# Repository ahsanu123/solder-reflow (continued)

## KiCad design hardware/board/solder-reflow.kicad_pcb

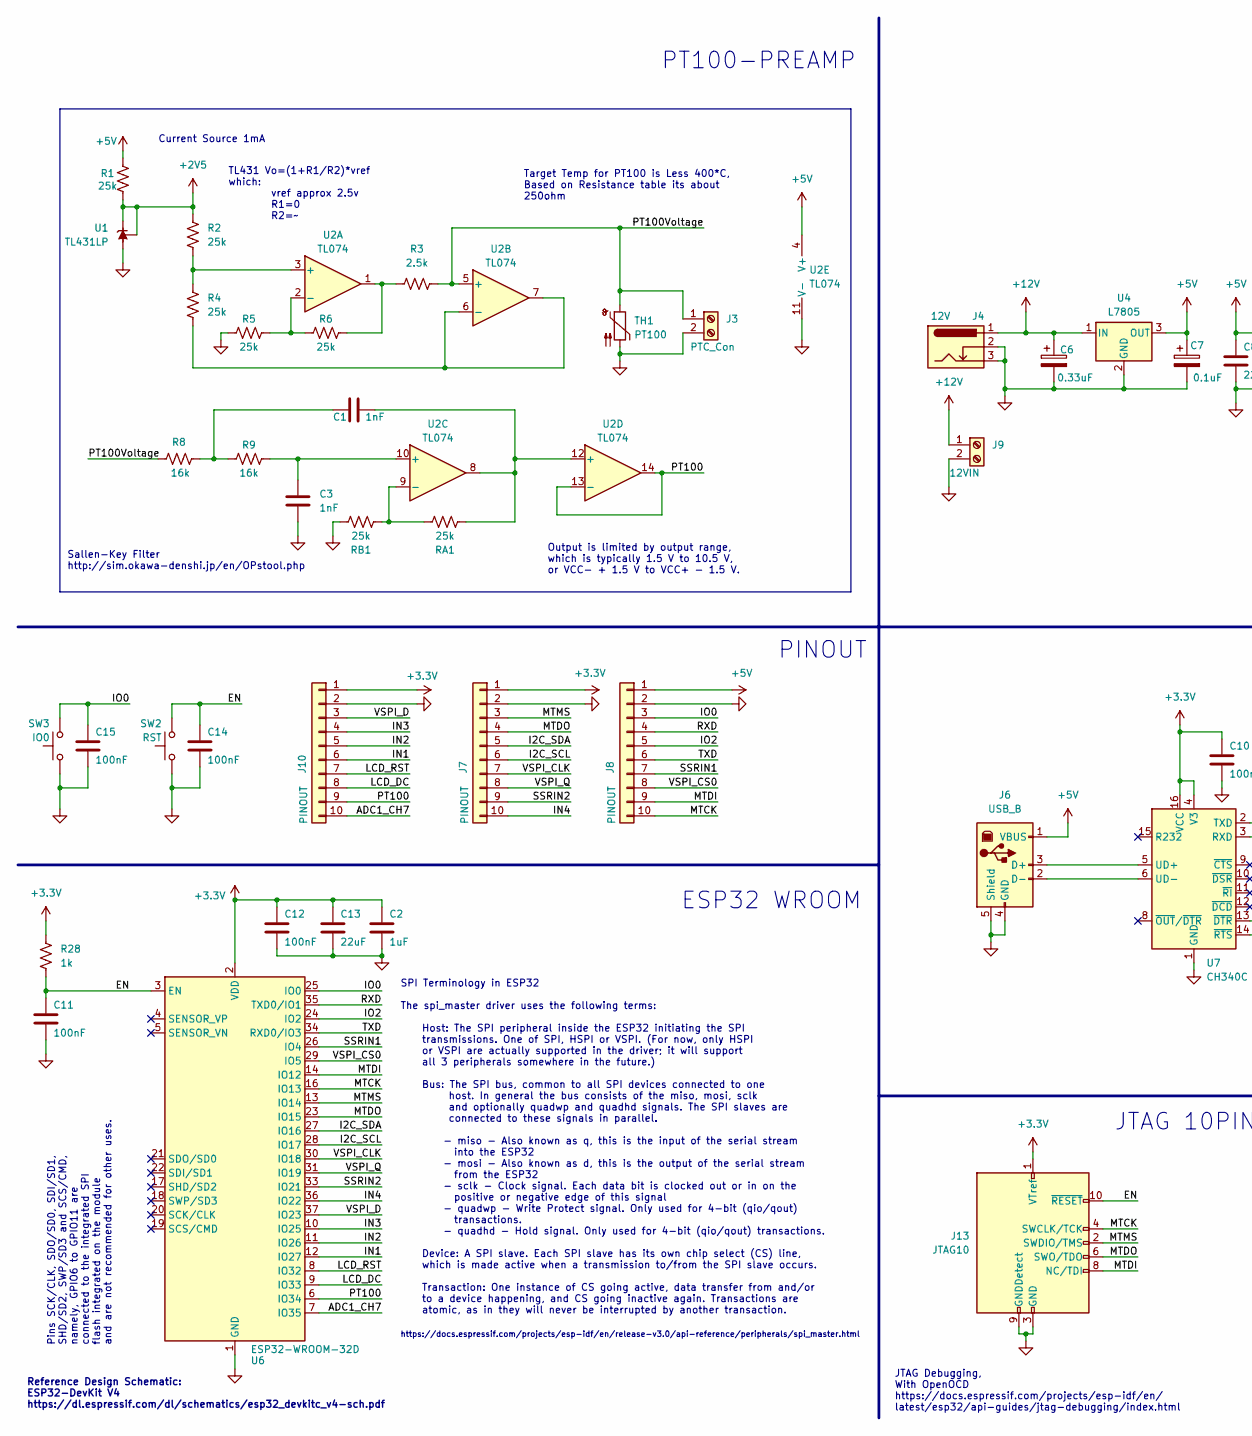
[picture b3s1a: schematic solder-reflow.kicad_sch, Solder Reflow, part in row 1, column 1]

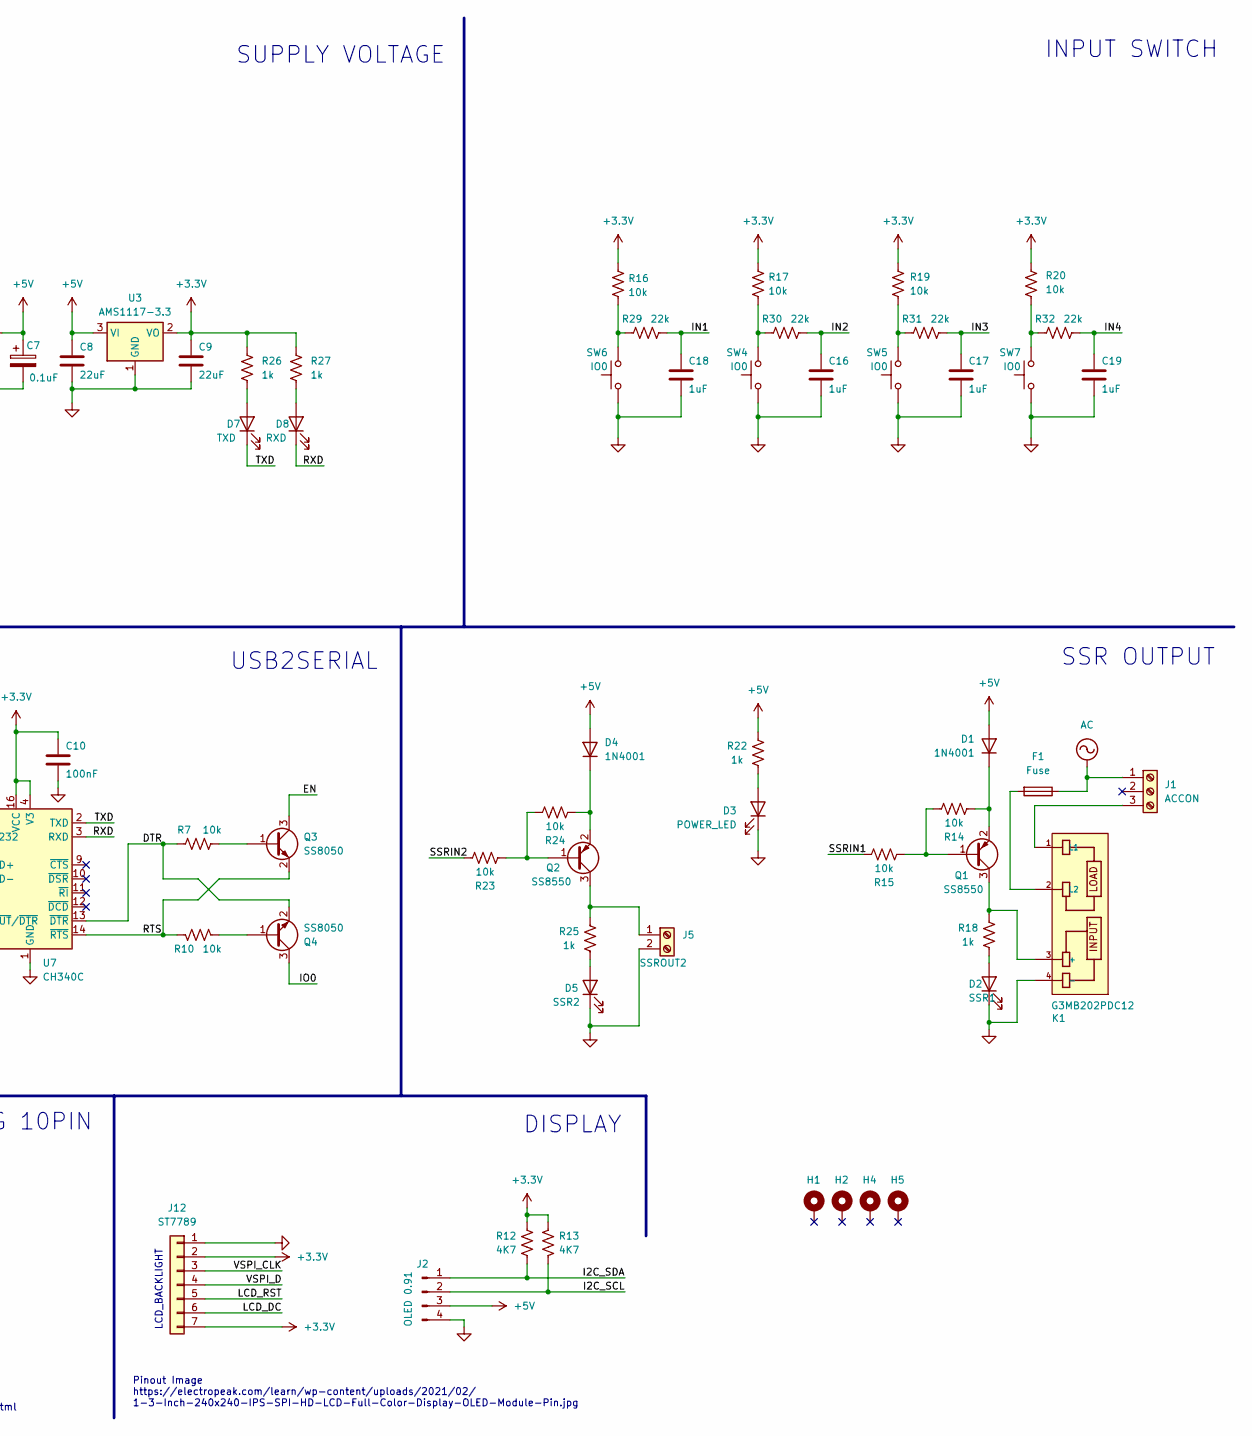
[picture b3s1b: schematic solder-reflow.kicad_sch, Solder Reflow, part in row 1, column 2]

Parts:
C1, C3: 1nF; C_1206_3216Metric_Pad1.33x1.80mm_HandSolder
C2, C16, C17, C18, C19: 1uF; C_1206_3216Metric_Pad1.33x1.80mm_HandSolder
C6: 0.33uF; C_1206_3216Metric_Pad1.33x1.80mm_HandSolder
C7: 0.1uF; C_1206_3216Metric_Pad1.33x1.80mm_HandSolder
C8, C9, C13: 22uF; C_1206_3216Metric_Pad1.33x1.80mm_HandSolder
C10, C11, C12, C14, C15: 100nF; C_1206_3216Metric_Pad1.33x1.80mm_HandSolder
D1, D4: 1N4001; D_SOD-123
D2: SSR1; LED_2010_5025Metric_Pad1.52x2.65mm_HandSolder
D3: POWER_LED; LED_2010_5025Metric_Pad1.52x2.65mm_HandSolder
D5: SSR2; LED_2010_5025Metric_Pad1.52x2.65mm_HandSolder
D7: TXD; LED_2010_5025Metric_Pad1.52x2.65mm_HandSolder
D8: RXD; LED_2010_5025Metric_Pad1.52x2.65mm_HandSolder
F1: Fuse; Fuseholder_Littelfuse_100_series_5x30mm
H1, H2, H4, H5: MountingHole_Pad; MountingHole_3.2mm_M3_DIN965_Pad
J1: ACCON; TerminalBlock_MetzConnect_Type055_RT01503HDWU_1x03_P5.00mm_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
J2: OLED 0.91; PinHeader_1x04_P2.54mm_Vertical
J3: PTC_Con; TerminalBlock_MetzConnect_Type011_RT05502HBWC_1x02_P5.00mm_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
J4: 12V; BarrelJack_Horizontal
J5: SSROUT2; TerminalBlock_MetzConnect_Type011_RT05502HBWC_1x02_P5.00mm_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
J6: USB_B; USB_B_OST_USB-B1HSxx_Horizontal
J7, J8, J10: PINOUT; PinHeader_1x10_P2.54mm_Vertical
J9: 12VIN; TerminalBlock_MetzConnect_Type011_RT05502HBWC_1x02_P5.00mm_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
J12: ST7789; PinSocket_1x07_P2.54mm_Vertical
J13: JTAG10; PinHeader_2x05_P2.54mm_Vertical
K1: G3MB202PDC12; RELAY_G3MB202PDC12; PARTREV N/A
Q1, Q2: SS8550; SOT-23_Handsoldering
Q3, Q4: SS8050; SOT-23_Handsoldering
R1, R2, R4, R5, R6: 25k; R_0805_2012Metric_Pad1.20x1.40mm_HandSolder
R3: 2.5k; R_0805_2012Metric_Pad1.20x1.40mm_HandSolder
R7, R10, R14, R15, R16, R17, R19, R20, R23, R24: 10k; R_0805_2012Metric_Pad1.20x1.40mm_HandSolder
R8, R9: 16k; R_0805_2012Metric_Pad1.20x1.40mm_HandSolder
R12, R13: 4K7; R_0805_2012Metric_Pad1.20x1.40mm_HandSolder
R18, R22, R25, R26, R27, R28: 1k; R_0805_2012Metric_Pad1.20x1.40mm_HandSolder
R29, R30, R31, R32: 22k; R_0805_2012Metric_Pad1.20x1.40mm_HandSolder
RA1: 25k; R_0805_2012Metric_Pad1.20x1.40mm_HandSolder
RB1: 25k; R_0805_2012Metric_Pad1.20x1.40mm_HandSolder
SW2: RST; SW_SPST_B3S-1000
SW3, SW4, SW5, SW6, SW7: IO0; SW_SPST_B3S-1000
TH1: PT100; TO-92-2_Horizontal2
U1: TL431LP; TO-92_Inline_Wide
U2: TL074; SOIC-14_3.9x8.7mm_P1.27mm
U3: AMS1117-3.3; SOT-223-3_TabPin2
U4: L7805; TO-220F-3_Horizontal_TabDown
U6: ESP32-WROOM-32D
U7: CH340C; SOIC-16_3.9x9.9mm_P1.27mm

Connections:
+2V5: R1.1, R2.1, U1.1 (REF), U1.3 (K)
+3.3V: C2.1, C9.1, C10.1, C12.1, C13.1, J7.1, J10.1, J12.2, J12.7, J13.1 (VTref), R12.2, R13.2, R16.1, R17.1, R19.1, R20.1, R26.1, R27.1, R28.1, U3.2 (VO), U6.2 (VDD), U7.4 (V3), U7.16 (VCC); also elsewhere on the board
+5V: C7.1, C8.1, D1.2 (A), D4.2 (A), J2.3, J6.1 (VBUS), J8.1, R1.2, R22.2, U2.4 (V+), U3.3 (VI), U4.3 (OUT)
+12V: C6.1, J4.1, J9.1, U4.1 (IN)
/ADC1_CH7: J10.10, U6.7 (IO35)
/DTR: Q4.2 (E), R7.2, U7.13 (~DTR)
/EN: C11.1, C14.1, J13.10 (~RESET), Q3.3 (C), R28.2, SW2.2, U6.3 (EN)
/I2C_SCL: J2.2, J7.6, R13.1, U6.28 (IO17)
/I2C_SDA: J2.1, J7.5, R12.1, U6.27 (IO16)
/IN1: C18.1, J10.6, R29.1, U6.12 (IO27)
/IN2: C16.1, J10.5, R30.1, U6.11 (IO26)
/IN3: C17.1, J10.4, R31.1, U6.10 (IO25)
/IN4: C19.1, J7.10, R32.1, U6.36 (IO22)
/IO0: C15.1, J8.3, Q4.3 (C), SW3.2, U6.25 (IO0)
/LCD_CS: J8.5, U6.24 (IO2); also elsewhere on the board
/LCD_DC: J10.8, J12.6, U6.9 (IO33); also elsewhere on the board
/LCD_RST: J10.7, J12.5, U6.8 (IO32); also elsewhere on the board
/MTCK: J8.10, J13.4 (SWCLK/TCK), U6.16 (IO13)
/MTDI: J8.9, J13.8 (NC/TDI), U6.14 (IO12)
/MTDO: J7.4, J13.6 (SWO/TDO), U6.23 (IO15)
/MTMS: J7.3, J13.2 (SWDIO/TMS), U6.13 (IO14)
/PT100: J10.9, U2.13 (-), U2.14, U6.6 (IO34)
/PT100Voltage: J3.1, R3.1, R8.2, TH1.1, U2.5 (+)
/RTS: Q3.2 (E), R10.2, U7.14 (~RTS)
/RXD: D8.1 (K), J8.4, U6.35 (TXD0/IO1), U7.3 (RXD)
/SSRIN1: J8.7, R15.1, U6.26 (IO4)
/SSRIN2: J7.9, R23.1, U6.33 (IO21)
/TXD: D7.1 (K), J8.6, U6.34 (RXD0/IO3), U7.2 (TXD)
/VSPI_CLK: J7.7, J12.3, U6.30 (IO18); also elsewhere on the board
/VSPI_CS0: J8.8, U6.29 (IO5)
/VSPI_D: J10.3, J12.4, U6.37 (IO23); also elsewhere on the board
/VSPI_Q: J7.8, U6.31 (IO19)
AC: F1.1, J1.1
GND: C2.2, C3.2, C6.2, C7.2, C8.2, C9.2, C10.2, C11.2, C12.2, C13.2, C14.2, C15.2, C16.2, C17.2, C18.2, C19.2, D2.1 (K), D3.1 (K), D5.1 (K), J2.4, J3.2, J4.2, J4.3, J5.2, J6.4 (GND), J6.5 (Shield), J7.2, J8.2, J9.2, J10.2, J12.1, J13.3 (GND), J13.5 (GND), J13.9 (GNDDetect), K1.4 (-), R5.1, RB1.1, SW2.1, SW3.1, SW4.1, SW5.1, SW6.1, SW7.1, TH1.2, U1.2 (A), U2.11 (V-), U3.1 (GND), U4.2 (GND), U6.1 (GND), U6.15 (GND), U6.38 (GND), U6.39 (GND), U7.1 (GND); also elsewhere on the board
unnamed: C1.2, R8.1, R9.2
unnamed: D1.1 (K), Q1.2 (E), R14.2
unnamed: D2.2 (A), R18.1
unnamed: D3.2 (A), R22.1
unnamed: D4.1 (K), Q2.2 (E), R24.2
unnamed: D5.2 (A), R25.1
unnamed: D7.2 (A), R26.2
unnamed: D8.2 (A), R27.2
unnamed: J1.3, K1.1 (L1)
unnamed: J5.1, Q2.3 (C), R25.2
unnamed: J6.3 (D+), U7.5 (UD+)
unnamed: J6.2 (D-), U7.6 (UD-)
unnamed: K1.3 (+), Q1.3 (C), R18.2
unnamed: F1.2, K1.2 (L2)
unnamed: Q1.1 (B), R14.1, R15.2
unnamed: Q2.1 (B), R23.2, R24.1
unnamed: Q3.1 (B), R7.1
unnamed: Q4.1 (B), R10.1
unnamed: R3.2, R6.1, U2.1
unnamed: R16.2, R29.2, SW6.2
unnamed: R17.2, R30.2, SW4.2
unnamed: R19.2, R31.2, SW5.2
unnamed: R20.2, R32.2, SW7.2
unnamed: R2.2, R4.1, U2.3 (+)
unnamed: R5.2, R6.2, U2.2 (-)
unnamed: R4.2, U2.6 (-), U2.7
unnamed: C3.1, R9.1, U2.10 (+)
unnamed: RA1.1, RB1.2, U2.9 (-)
unnamed: C1.1, RA1.2, U2.8, U2.12 (+)

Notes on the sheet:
Sallen-Key Filter http://sim.okawa-denshi.jp/en/OPstool.php
Reference Design Schematic: ESP32-DevKit V4 https://dl.espressif.com/dl/schematics/esp32_devkitc_v4-sch.pdf
SUPPLY VOLTAGE
JTAG 10PIN
Output is limited by output range, which is typically 1.5 V to 10.5 V, or VCC- + 1.5 V to VCC+ - 1.5 V.
Pinout Image https://electropeak.com/learn/wp-content/uploads/2021/02/ 1-3-Inch-240x240-IPS-SPI-HD-LCD-Full-Color-Display-OLED-Module-Pin.jpg
ESP32 WROOM
PT100-PREAMP
DISPLAY
Pins SCK/CLK, SDO/SD0, SDI/SD1, SHD/SD2, SWP/SD3 and SCS/CMD, namely, GPIO6 to GPIO11 are connected to the integrated SPI flash integrated on the module and are not recommended for other uses.
TL431 Vo=(1+R1/R2)*vref which: vref approx 2.5v R1=0 R2=~
Target Temp for PT100 is Less 400*C, Based on Resistance table its about 250ohm
PINOUT
Current Source 1mA
JTAG Debugging, With OpenOCD https://docs.espressif.com/projects/esp-idf/en/ latest/esp32/api-guides/jtag-debugging/index.html
SPI Terminology in ESP32 The spi_master driver uses the following terms: Host: The SPI peripheral inside the ESP32 initiating the SPI transmissions. One of SPI, HSPI or VSPI. (For now, only HSPI or VSPI are actually supported in the driver; it will support all 3 peripherals somewhere in the future.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
LCD_BACKLIGHT
USB2SERIAL
INPUT SWITCH
SSR OUTPUT

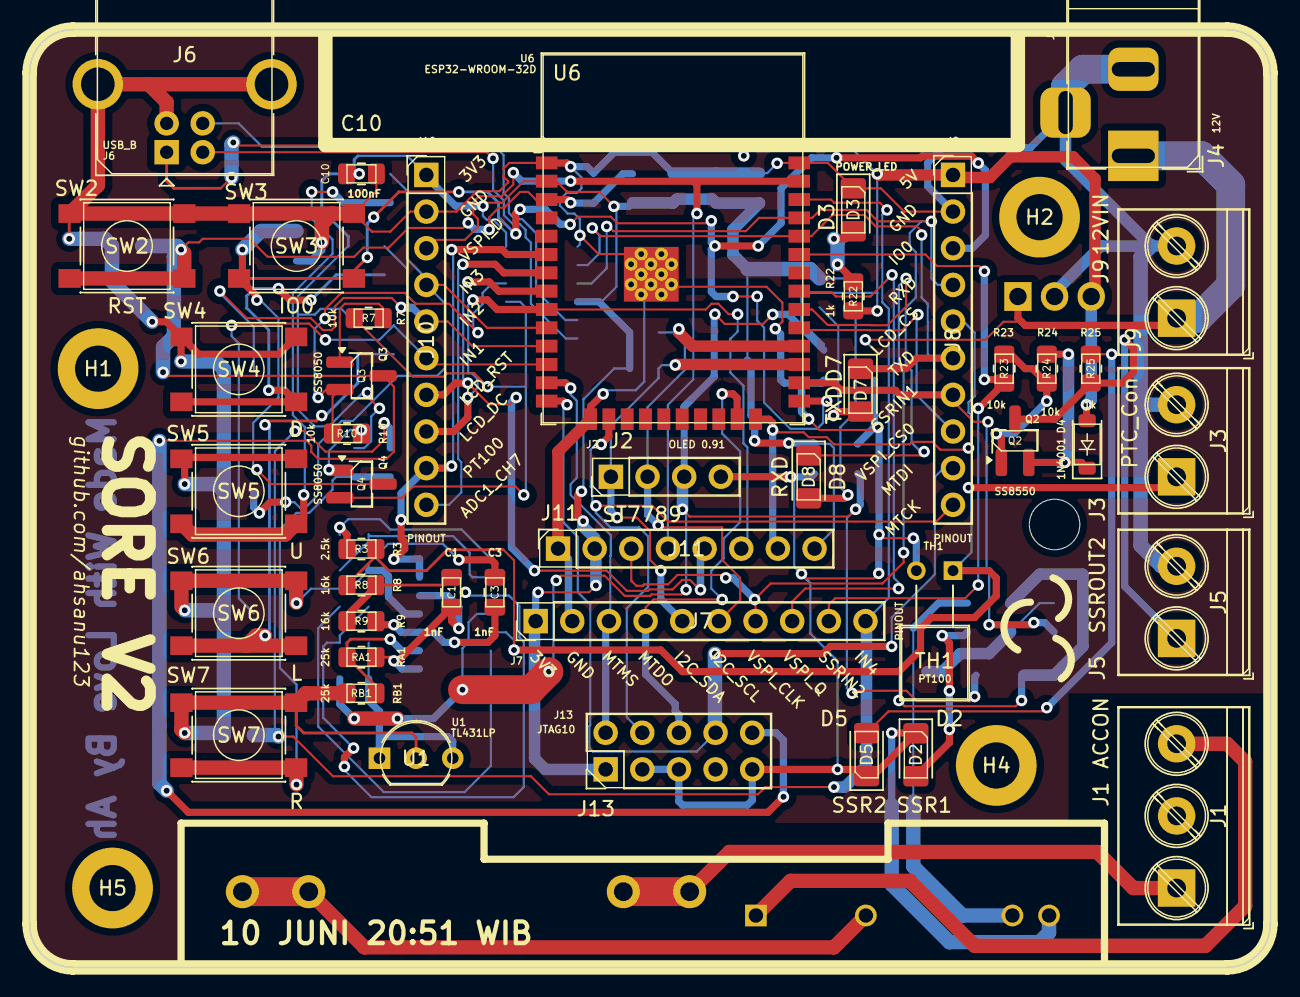
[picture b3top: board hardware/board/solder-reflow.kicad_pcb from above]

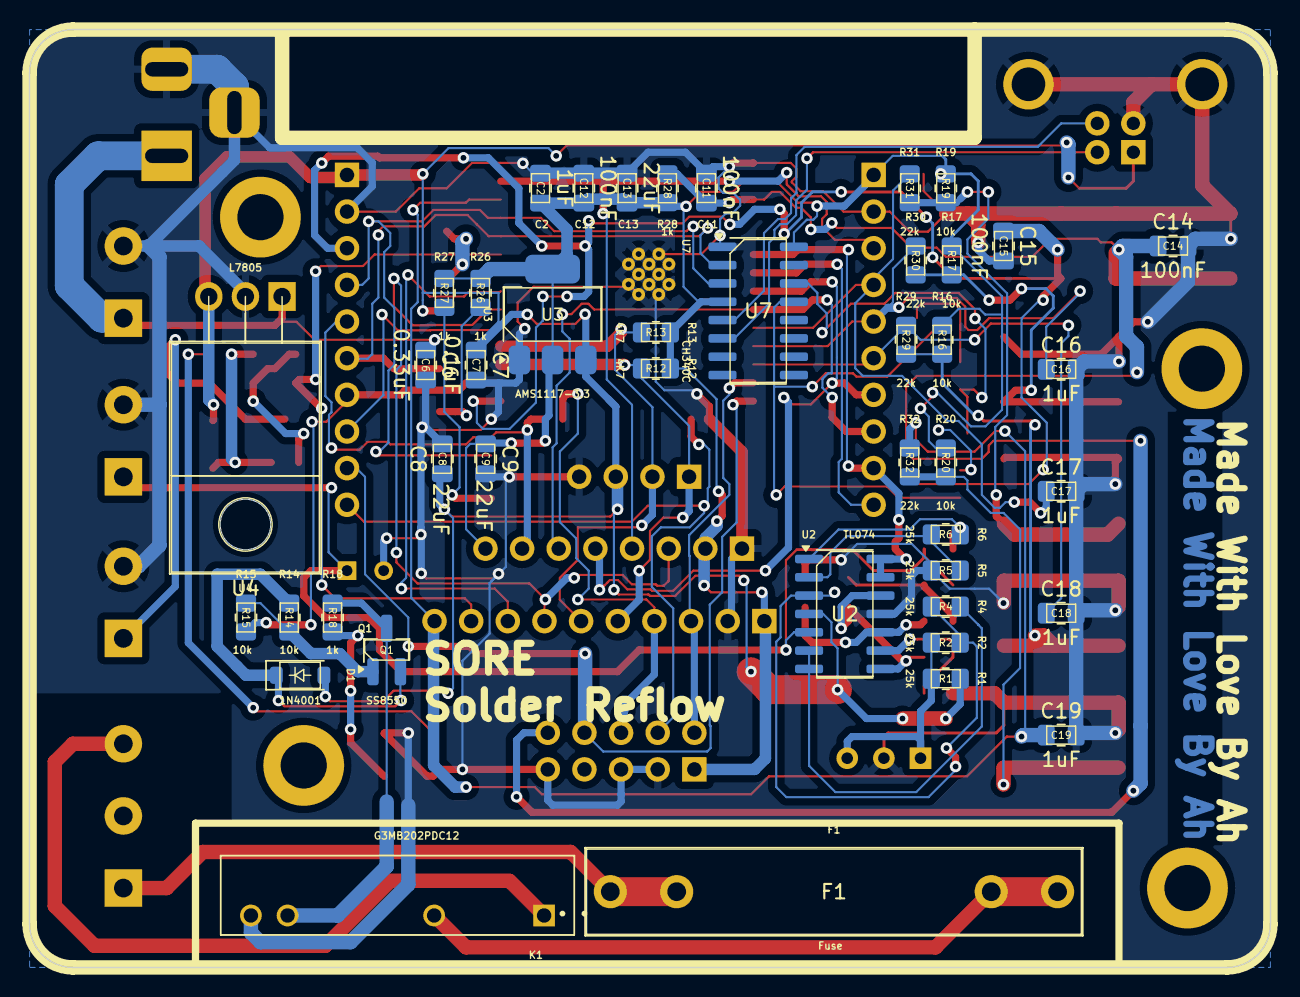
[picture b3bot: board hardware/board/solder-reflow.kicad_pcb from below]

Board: 2 copper layers, 86.0 x 65.0 mm, 91 parts (43 on the bottom side), 63 nets.

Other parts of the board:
J11: ST7789; PinSocket_1x08_P2.54mm_Vertical

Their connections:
+3.3V: J11.2, J11.8; also elsewhere on the board
/LCD_CS: J11.7; also elsewhere on the board
/LCD_DC: J11.6; also elsewhere on the board
/LCD_RST: J11.5; also elsewhere on the board
/VSPI_CLK: J11.3; also elsewhere on the board
/VSPI_D: J11.4; also elsewhere on the board
GND: J11.1; also elsewhere on the board

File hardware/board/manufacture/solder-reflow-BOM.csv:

"Id";"Designator";"Footprint";"Quantity";"Designation";"Supplier and ref";
1;"J9";"TerminalBlock_Phoenix_PT-1,5-2-5.0-H_1x02_P5.00mm_Horizontal";1;"12VIN";;;
2;"J3";"TerminalBlock_Phoenix_PT-1,5-2-5.0-H_1x02_P5.00mm_Horizontal";1;"PTC_Con";;;
3;"J5";"TerminalBlock_Phoenix_PT-1,5-2-5.0-H_1x02_P5.00mm_Horizontal";1;"SSROUT2";;;
4;"D8";"LED_2010_5025Metric_Pad1.52x2.65mm_HandSolder";1;"RXD";;;
5;"R9,R8";"R_0805_2012Metric_Pad1.20x1.40mm_HandSolder";2;"16k";;;
6;"H1,H2,H5,H4";"MountingHole_3.2mm_M3_DIN965_Pad";4;"MountingHole_Pad";;;
7;"R23,R10,R7,R24,R14,R17,R15,R20,R19,R16";"R_0805_2012Metric_Pad1.20x1.40mm_HandSolder";10;"10k";;;
8;"U1";"TO-92_Inline_Wide";1;"TL431LP";;;
9;"U6";"ESP32-WROOM-32D";1;"ESP32-WROOM-32D";;;
10;"D3";"LED_2010_5025Metric_Pad1.52x2.65mm_HandSolder";1;"POWER_LED";;;
11;"RA1,RB1,R6,R4,R2,R5,R1";"R_0805_2012Metric_Pad1.20x1.40mm_HandSolder";7;"25k";;;
12;"J6";"USB_B_OST_USB-B1HSxx_Horizontal";1;"USB_B";;;
13;"R25,R22,R26,R27,R28,R18";"R_0805_2012Metric_Pad1.20x1.40mm_HandSolder";6;"1k";;;
14;"SW2";"SW_SPST_B3S-1000";1;"RST";;;
15;"Q3,Q4";"SOT-23_Handsoldering";2;"SS8050";;;
16;"C10,C11,C15,C14,C12";"C_1206_3216Metric_Pad1.33x1.80mm_HandSolder";5;"100nF";;;
17;"SW5,SW7,SW6,SW4,SW3";"SW_SPST_B3S-1000";5;"IO0";;;
18;"C3,C1";"C_1206_3216Metric_Pad1.33x1.80mm_HandSolder";2;"1nF";;;
19;"J13";"PinHeader_2x05_P2.54mm_Vertical";1;"JTAG10";;;
20;"J12";"PinSocket_1x07_P2.54mm_Vertical";1;"ST7789";;;
21;"R3";"R_0805_2012Metric_Pad1.20x1.40mm_HandSolder";1;"2.5k";;;
22;"J8,J7,J10";"PinHeader_1x10_P2.54mm_Vertical";3;"PINOUT";;;
23;"J1";"TerminalBlock_MetzConnect_Type055_RT01503HDWU_1x03_P5.00mm_Horizontal";1;"ACCON";;;
24;"D2";"LED_2010_5025Metric_Pad1.52x2.65mm_HandSolder";1;"SSR1";;;
25;"J2";"PinHeader_1x04_P2.54mm_Vertical";1;"OLED 0.91";;;
26;"D7";"LED_2010_5025Metric_Pad1.52x2.65mm_HandSolder";1;"TXD";;;
27;"Q2,Q1";"SOT-23_Handsoldering";2;"SS8550";;;
28;"J4";"BarrelJack_Horizontal";1;"12V";;;
29;"D4,D1";"D_SOD-123";2;"1N4001";;;
30;"D5";"LED_2010_5025Metric_Pad1.52x2.65mm_HandSolder";1;"SSR2";;;
31;"R31,R32,R29,R30";"R_0805_2012Metric_Pad1.20x1.40mm_HandSolder";4;"22k";;;
32;"C19,C17,C16,C18,C2";"C_1206_3216Metric_Pad1.33x1.80mm_HandSolder";5;"1uF";;;
33;"U7";"SOIC-16_3.9x9.9mm_P1.27mm";1;"CH340C";;;
34;"R12,R13";"R_0805_2012Metric_Pad1.20x1.40mm_HandSolder";2;"4K7";;;
35;"C8,C13,C9";"C_1206_3216Metric_Pad1.33x1.80mm_HandSolder";3;"22uF";;;
36;"U3";"SOT-223-3_TabPin2";1;"AMS1117-3.3";;;
37;"C6";"C_1206_3216Metric_Pad1.33x1.80mm_HandSolder";1;"0.33uF";;;
38;"TH1";"TO-92-2_Horizontal2";1;"PT100";;;
39;"K1";"RELAY_G3MB202PDC12";1;"G3MB202PDC12";;;
40;"F1";"Fuseholder_Littelfuse_100_series_5x30mm";1;"Fuse";;;
41;"C7";"C_1206_3216Metric_Pad1.33x1.80mm_HandSolder";1;"0.1uF";;;
42;"U2";"SOIC-14_3.9x8.7mm_P1.27mm";1;"TL074";;;
43;"U4";"TO-220F-3_Horizontal_TabDown";1;"L7805";;;

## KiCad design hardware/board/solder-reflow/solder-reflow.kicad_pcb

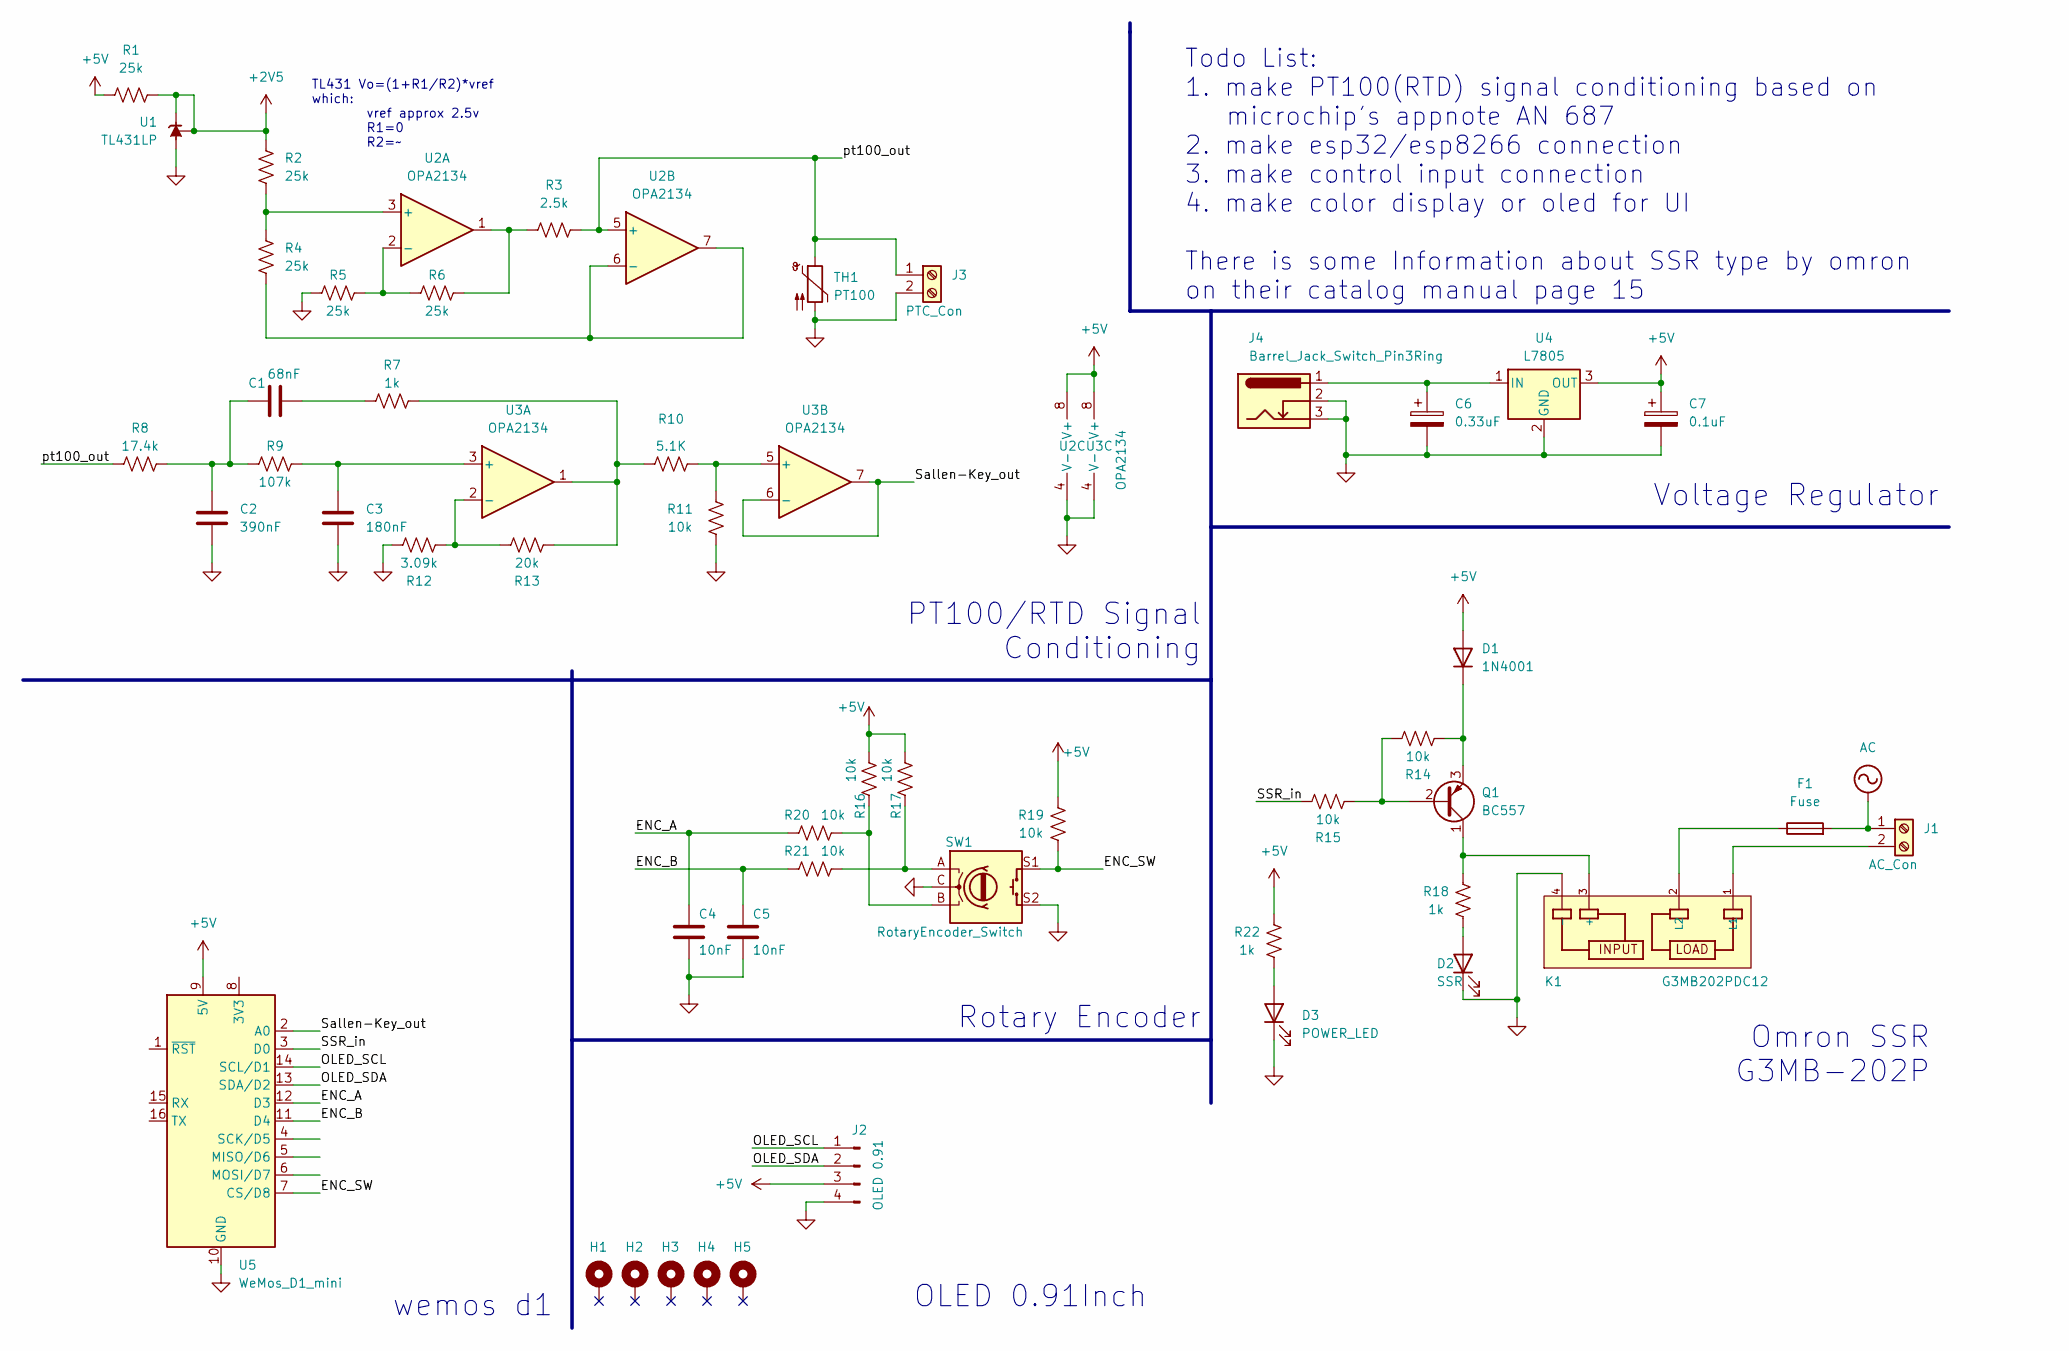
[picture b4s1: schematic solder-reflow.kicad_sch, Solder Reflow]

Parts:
C1: 68nF; C_Disc_D4.3mm_W1.9mm_P5.00mm
C2: 390nF; C_Disc_D4.3mm_W1.9mm_P5.00mm
C3: 180nF; C_Disc_D4.3mm_W1.9mm_P5.00mm
C4, C5: 10nF; C_Disc_D4.3mm_W1.9mm_P5.00mm
C6: 0.33uF; CP_Radial_D6.3mm_P2.50mm
C7: 0.1uF; CP_Radial_D6.3mm_P2.50mm
D1: 1N4001; D_DO-41_SOD81_P10.16mm_Horizontal
D2: SSR; LED_D5.0mm
D3: POWER_LED; LED_D5.0mm
F1: Fuse; Fuseholder_Littelfuse_100_series_5x30mm
H1, H2, H3, H4, H5: MountingHole_Pad; MountingHole_3.2mm_M3_DIN965_Pad
J1: AC_Con; TerminalBlock_MetzConnect_Type011_RT05502HBWC_1x02_P5.00mm_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
J2: OLED 0.91; PinHeader_1x04_P2.54mm_Vertical
J3: PTC_Con; TerminalBlock_MetzConnect_Type011_RT05502HBWC_1x02_P5.00mm_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
J4: Barrel_Jack_Switch_Pin3Ring; BarrelJack_Horizontal
K1: G3MB202PDC12; RELAY_G3MB202PDC12; PARTREV N/A
Q1: BC557; TO-92_Inline_Wide
R1, R2, R4, R5, R6: 25k; R_Axial_DIN0207_L6.3mm_D2.5mm_P10.16mm_Horizontal
R3: 2.5k; R_Axial_DIN0207_L6.3mm_D2.5mm_P10.16mm_Horizontal
R7, R18, R22: 1k; R_Axial_DIN0207_L6.3mm_D2.5mm_P10.16mm_Horizontal
R8: 17.4k; R_Axial_DIN0207_L6.3mm_D2.5mm_P10.16mm_Horizontal
R9: 107k; R_Axial_DIN0207_L6.3mm_D2.5mm_P10.16mm_Horizontal
R10: 5.1K; R_Axial_DIN0207_L6.3mm_D2.5mm_P10.16mm_Horizontal
R11, R14, R15, R16, R17, R19, R20, R21: 10k; R_Axial_DIN0207_L6.3mm_D2.5mm_P10.16mm_Horizontal
R12: 3.09k; R_Axial_DIN0207_L6.3mm_D2.5mm_P10.16mm_Horizontal
R13: 20k; R_Axial_DIN0207_L6.3mm_D2.5mm_P10.16mm_Horizontal
SW1: RotaryEncoder_Switch; RotaryEncoder_Alps_EC11E-Switch_Vertical_H20mm
TH1: PT100; TO-92-2_Horizontal2
U1: TL431LP; TO-92_Inline_Wide
U2, U3: OPA2134; DIP-8_W7.62mm_LongPads
U4: L7805; TO-220F-3_Horizontal_TabDown
U5: WeMos_D1_mini; WEMOS_D1_mini_light

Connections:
+2V5: R1.2, R2.1, U1.1 (REF), U1.3 (K)
+5V: C7.1, D1.2 (A), J2.3, R1.1, R16.2, R17.2, R19.2, R22.2, U2.8 (V+), U3.8 (V+), U4.3 (OUT), U5.9 (5V)
/ENC_A: C4.1, R20.2, U5.12 (D3)
/ENC_B: C5.1, R21.2, U5.11 (D4)
/ENC_SW: R19.1, SW1.S1, U5.7 (CS/D8)
/OLED_SCL: J2.1, U5.14 (SCL/D1)
/OLED_SDA: J2.2, U5.13 (SDA/D2)
/SSR_in: R15.1, U5.3 (D0)
/Sallen-Key_out: U3.6 (-), U3.7, U5.2 (A0)
/pt100_out: J3.1, R3.1, R8.2, TH1.1, U2.5 (+)
AC: F1.2, J1.1
GND: C2.2, C3.2, C4.2, C5.2, C6.2, C7.2, D2.1 (K), D3.1 (K), J2.4, J3.2, J4.2, J4.3, K1.4 (-), R5.1, R11.1, R12.1, SW1.C, SW1.S2, TH1.2, U1.2 (A), U2.4 (V-), U3.4 (V-), U4.2 (GND), U5.10 (GND)
unnamed: C1.1, R7.2
unnamed: C1.2, C2.1, R8.1, R9.2
unnamed: D1.1 (K), Q1.3 (E), R14.2
unnamed: D2.2 (A), R18.1
unnamed: D3.2 (A), R22.1
unnamed: J1.2, K1.1 (L1)
unnamed: K1.3 (+), Q1.1 (C), R18.2
unnamed: F1.1, K1.2 (L2)
unnamed: Q1.2 (B), R14.1, R15.2
unnamed: R3.2, R6.1, U2.1
unnamed: R7.1, R10.1, R13.2, U3.1
unnamed: R16.1, R20.1, SW1.B
unnamed: R17.1, R21.1, SW1.A
unnamed: R2.2, R4.1, U2.3 (+)
unnamed: R5.2, R6.2, U2.2 (-)
unnamed: R4.2, U2.6 (-), U2.7
unnamed: C3.1, R9.1, U3.3 (+)
unnamed: R12.2, R13.1, U3.2 (-)
unnamed: R10.2, R11.2, U3.5 (+)
unnamed: C6.1, J4.1, U4.1 (IN)

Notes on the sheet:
Voltage Regulator
wemos d1
PT100/RTD Signal Conditioning
OLED 0.91Inch
TL431 Vo=(1+R1/R2)*vref which: vref approx 2.5v R1=0 R2=~
Todo List: 1. make PT100(RTD) signal conditioning based on microchip's appnote AN 687 2. make esp32/esp8266 connection 3. make control input connection 4. make color display or oled for UI There is some Information about SSR type by omron on their catalog manual page 15
Rotary Encoder
Omron SSR G3MB-202P

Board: 2 copper layers, 51 parts (0 on the bottom side), 32 nets, no tracks yet.

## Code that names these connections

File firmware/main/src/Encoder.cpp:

#include "Encoder.h"
#include "gpio.h"
#include <cstdint>

#ifndef INCLUDE_SRC_ENCODER_CPP_
#define INCLUDE_SRC_ENCODER_CPP_

Encoder::Encoder() {

  gpio_config_t enc_ab_sw = {.pin_bit_mask =
                                 GPIO_Pin_0 | GPIO_Pin_2 | GPIO_Pin_15,
                             .mode = GPIO_MODE_INPUT,
                             .pull_up_en = GPIO_PULLUP_DISABLE,
                             .pull_down_en = GPIO_PULLDOWN_DISABLE,
                             .intr_type = GPIO_INTR_DISABLE};
  gpio_config(&enc_ab_sw);
}

float Encoder::setToTarget(float *target) {
  *target = this->_target;
  return *target;
}

float Encoder::decodeEncoder() {
  /*
   * |New state | Old State|
   * |  3 |  2  |  1 |  0  |
   *
   * */
  uint8_t rawData = (1 << !gpio_get_level(ENC_A)) | !gpio_get_level(ENC_B);
  uint8_t state = this->_oldState & 0x03;

  if (rawData & 0x04)
    state |= 0x04;
  if (rawData & 0x08)
    state |= 0x08;

  switch (state) {
  case 0:
  case 5:
  case 10:
  case 15:
    break;
  case 1:
  case 7:
  case 8:
  case 14:
    this->position += this->step;

    if (this->connectedVariable) {
      *this->connectedVariable += this->step;
    } else {
    }
    this->connectedMenu->up();
    break;
  case 2:
  case 4:
  case 11:
  case 13:
    this->position -= this->step;

    if (this->connectedVariable) {
      *this->connectedVariable -= this->step;
    } else {
    }
    this->connectedMenu->down();
    break;
  case 3:
  case 12:
    this->position += this->step * 2;

    if (this->connectedVariable) {
      *this->connectedVariable += this->step * 2;
    } else {
    }
    this->connectedMenu->up();
    break;
  default:
    this->position -= this->step * 2;

    if (this->connectedVariable) {
      *this->connectedVariable -= this->step * 2;
    } else {
    }
    this->connectedMenu->down();
    break;
  }

  this->_oldState = state >> 2;

  return this->position;
};

bool Encoder::decodeSwitch(float &target) {

  /*
   * | OLD || NEW |
   * |  0  ||  0  | no change
   * |  0  ||  1  | toggled
   * |  1  ||  0  | change
   * |  1  ||  1  | no change
   * */

  bool state = gpio_get_level(ENC_SW);

  uint8_t current = this->_oldSwitchState + state;

  if (current == 1) {
    this->_oldSwitchState = state << 1;
    this->switchState = !this->switchState;

    if (this->switchState) {
      this->connectedVariable = &target;
    } else {
      this->connectedVariable = NULL;
    }

    return this->switchState;
  } else if (current == 2) {
    this->_oldSwitchState = state;
    return this->switchState;
  } else {
    return this->switchState;
  }
}
#endif // INCLUDE_SRC_ENCODER_CPP_

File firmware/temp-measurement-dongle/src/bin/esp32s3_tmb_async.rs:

#![no_std]
#![no_main]
#![deny(
    clippy::mem_forget,
    reason = "mem::forget is generally not safe to do with esp_hal types, especially those \
    holding buffers for the duration of a data transfer."
)]
#![deny(clippy::large_stack_frames)]

use alloc::boxed::Box;
use defmt::info;
use embassy_executor::Spawner;
use embassy_time::Timer;
use embedded_hal_bus::spi::ExclusiveDevice;
use esp_hal::clock::CpuClock;
use esp_hal::delay::Delay;
use esp_hal::dma::{DmaRxBuf, DmaTxBuf};
use esp_hal::dma_buffers;
use esp_hal::gpio::{Level, Output, OutputConfig};
use esp_hal::spi::Mode;
use esp_hal::spi::master::Config;
use esp_hal::spi::master::Spi;
use esp_hal::time::Rate;
use esp_hal::timer::timg::TimerGroup;
use mipidsi::options::{ColorOrder, Orientation, Rotation};
use slint::ComponentHandle;
use slint::platform::software_renderer::{MinimalSoftwareWindow, RepaintBufferType};
use static_cell::StaticCell;
use tmb_ui::TmbApp;
use tmd::platforms::esp32s3_async::backend::Esp32AsyncBackend;
use tmd::platforms::esp32s3_async::draw_buffer::DrawBuffer;
use {esp_backtrace as _, esp_println as _};

extern crate alloc;

// This creates a default app-descriptor required by the esp-idf bootloader.
// For more information see: <https://docs.espressif.com/projects/esp-idf/en/stable/esp32/api-reference/system/app_image_format.html#application-description>
esp_bootloader_esp_idf::esp_app_desc!();

static INTERFACE_BUFFER: StaticCell<[u8; 312]> = StaticCell::new();

static DISPLAY_HEIGHT: usize = 172;
static DISPLAY_WIDTH: usize = 320;

#[allow(
    clippy::large_stack_frames,
    reason = "it's not unusual to allocate larger buffers etc. in main"
)]
#[esp_rtos::main]
async fn main(_spawner: Spawner) {
    esp_alloc::heap_allocator!(#[esp_hal::ram(reclaimed)] size: 73744);

    let config = esp_hal::Config::default().with_cpu_clock(CpuClock::_80MHz);
    let peripherals = esp_hal::init(config);

    let timg0 = TimerGroup::new(peripherals.TIMG0);
    esp_rtos::start(timg0.timer0);

    let lcd_dc = peripherals.GPIO15;
    let lcd_cs = peripherals.GPIO10;
    let lcd_rst = peripherals.GPIO14;
    let lcd_blk = peripherals.GPIO16;

    let scl_mosi = peripherals.GPIO13;
    let scl_sck = peripherals.GPIO12;
    let scl_miso = peripherals.GPIO11;

    let dma_channel = peripherals.DMA_CH0;

    let lcd_cs = Output::new(lcd_cs, Level::Low, OutputConfig::default());
    let lcd_dc = Output::new(lcd_dc, Level::Low, OutputConfig::default());
    let lcd_rst = Output::new(lcd_rst, Level::Low, OutputConfig::default());
    let mut lcd_blk = Output::new(lcd_blk, Level::Low, OutputConfig::default());

    let (rx_buffer, rx_descriptors, tx_buffer, tx_descriptors) = dma_buffers!(2048);
    let dma_rx_buf = DmaRxBuf::new(rx_descriptors, rx_buffer).unwrap();
    let dma_tx_buf = DmaTxBuf::new(tx_descriptors, tx_buffer).unwrap();

    let spi_bus = Spi::new(
        peripherals.SPI2,
        Config::default()
            .with_frequency(Rate::from_mhz(1))
            .with_mode(Mode::_0),
    )
    .unwrap()
    .with_sck(scl_sck)
    .with_mosi(scl_mosi)
    .with_miso(scl_miso)
    .with_dma(dma_channel)
    .with_buffers(dma_rx_buf, dma_tx_buf);

    let interface_buffer = INTERFACE_BUFFER.init([0u8; 312]);

    let mut delay = Delay::new();
    let spi_device = ExclusiveDevice::new(spi_bus, lcd_cs, delay).unwrap();

    let di = mipidsi::interface::SpiInterface::new(spi_device, lcd_dc, interface_buffer);

    let st7789 = mipidsi::Builder::new(tmd::display_models::st7789_modified::ST7789, di)
        .display_size(DISPLAY_WIDTH as u16, DISPLAY_HEIGHT as u16)
        .orientation(Orientation::new().rotate(Rotation::Deg270))
        .color_order(ColorOrder::Rgb)
        .display_offset(33, 340)
        .invert_colors(mipidsi::options::ColorInversion::Inverted)
        .reset_pin(lcd_rst)
        .init(&mut delay)
        .expect("fail to build display st7789");

    let mut draw_buffer = DrawBuffer::new(st7789);

    let window = MinimalSoftwareWindow::new(RepaintBufferType::ReusedBuffer);
    window.set_size(slint::PhysicalSize::new(
        DISPLAY_WIDTH as u32,
        DISPLAY_HEIGHT as u32,
    ));

    let backend = Box::new(Esp32AsyncBackend::new(window.clone()));
    slint::platform::set_platform(backend).expect("fail when set platform");

    info!("slint gui setup complete");

    lcd_blk.set_high();

    let tmb_app = TmbApp::new().expect("cant create Tmb Application");
    tmb_app.show().expect("unable to show tmb_app");

    loop {
        slint::platform::update_timers_and_animations();

        window.draw_if_needed(|renderer| {
            info!("render by line!");
            renderer.render_by_line(&mut draw_buffer);
        });

        Timer::after_millis(50).await;
    }
}

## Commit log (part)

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2024-03-01 staged finished schematic v1
2024-03-01 finish pcb layout
    add a backup zip
2024-03-06 finishing up routing and make a schematic pdf output
2024-03-06 rotate wemos d1 mini
2024-03-07 route rotated wemos and make order to jlc pcb
2024-03-08 export 3d step file
2024-03-12 Create LICENSE
2024-03-31 update value of one resistor
2024-03-31 copied uart example from esp8266 repo
2024-03-31 update build using cmake
    ok
2024-04-02 adding menu menulist menuitem basic class
2024-04-04 adding ssd1306 old library and add rotary encoder header
2024-04-04 [5-4-0538] adding ssd1306 and fix find use std::find_if
2024-04-05 [5-4-0733] add PT100 class
2024-04-05 [5-4-1909] adding i2c and lcdgfx back to repo, success to build
2024-04-06 [6-4-2024] adding simple control scheme and clang-format
2024-04-06 [6-4-2342] adding plot function, and simple drawing
2024-04-07 [6-7-1857] adding gradient and turnOffWithDelay
2024-04-07 [7-4-2212] create first todo revision
2024-04-08 [8-4-1200] make ssd1306 work
2024-04-12 [12-4-0738] adding lot of garbage code
2024-04-12 [12-4-1911] adding really bad toggle button functionality
2024-06-03 [4-6-0403] commit bad code
2024-06-04 [4-6-0739] add revision feature
2024-06-04 update revision spesification
2024-06-04 [5-6-0014] adding several io connection
2024-06-05 [5-6-0703] adding st7789 schematic
2024-06-05 [6-6-0359] finish first revision, need to review
2024-06-06 [6-7-1245] finish first layout, need to review
2024-06-08 [8-06-0716] finish up layout plus adding several random graphic
2024-06-08 [8-06-1357] finish routing, next do second review
2024-06-08 add back button
2024-06-10 [10-06-2138] tune silkscreen and track width
2024-06-15 [15-06-1731] adding gerber
2024-06-15 [15-06-2201] update readme and add schematic svg
2024-06-15 update schematic svg background color
2024-07-12 add image
2024-07-12 upload pic
2024-07-14 update firmware to version 2
2024-07-22 sync
2024-07-22 update lur
2024-07-22 update again
2024-07-22 copied adc continuous from esp32 exampel
2024-07-22 add some adc definition
2024-07-23 [23-07-24] add ADCDevice class to simplify adc initialization
2024-07-26 check GPIO input/output and add tune reference
2024-07-27 to wait st7789 use SDL2 to learn lvgl
2024-07-27 [27-07-1734] try to debug with Jlink Jtag (fail)
2024-07-27 update before crash
2024-07-28 add debugging section on README.md
2024-07-28 add svd and gdbinitt
2024-07-28 rename gdbinit
2024-08-24 add freertos coding standard referrence
2024-08-27 copied fsm into repo
2024-08-27 add mastering freertos kernel
2024-08-27 compiled fsm
2024-08-27 fsm on off example worked
2024-08-29 add Gpio Device class
2024-08-29 use cpp version??
2024-08-29 GPIO as Input with callback worked
2024-08-30 add new adc class, still not work as expected
2024-09-01 backup before learn freertos
2024-09-01 look at readme
2024-09-01 remove rtos note from rtos folder
2024-09-01 add adcQUEUE, still lot of error
2024-09-02 adc queue worked, plot still noisy, does plot really look like this
2024-09-14 add adc reading with little conversion, still not correctly working
2024-09-15 adding lvgl submodule
2024-09-15 add managed component with idf.py
2024-09-15 remove lvgl repo from git submodule
    update submodule again
2024-09-15 added readme to managed_components foldeer
2024-09-15 removee compile_command.json and start to make lvgl example
2024-09-15 lvgl esp32 port compiled but trigering watchdog, still investigating
2024-09-15 lvgl_port_init() stack on waiting semaphore???
2024-10-03 backup before try change to v8
2024-10-04 at least now lvgl worked (still crash)
2024-10-05 ok, lvgl working now, but task lock make watchdog trigered
2024-10-05 add spinner
2024-10-05 ok lvgl worked now
2024-10-05 try to create input device (button) still fail
2024-10-06 lvgl input button worked!!, need to tweak
2024-10-06 simple button navigation worked!!!
2024-10-30 [10-30-2007] sampling data from heater
    move sampled data into new folder
    Update README.md
    Update README.md
2024-11-02 [11-01-1113] estimate transfer function from raw data
    Update README.md
    Update README.md
    nit delay value
2024-11-03 [11-01-1113] estimate transfer function from raw data
    Update README.md
    Update README.md
    nit delay value
    Update README.md
2024-11-03 [10-30-2007] sampling data from heater
    move sampled data into new folder
    Update README.md
    Update README.md
    Update README.md
2024-11-09 [11-03-1414] playing with PID constant
    update data
    Update README.md
    Update README.md
2024-11-10 [11-03-2055] control work now (use PI controller)
    nit
    nit
2025-06-11 [06-11-2010] remove lvgl v1 and v2 firmware
2025-06-11 [06-11-2033] add sore tui to make simulator
2025-06-11 [06-11-2101] scafold esp project with embassy and defmt, use esp-generate
    esp-generate --chip esp32 -o alloc -o embassy -o defmt -o unstable-hal
    Sore-v3
2025-09-13 chore: duplicating v1 to make v3
2025-09-13 feat: start creating schematic with esp32-s3 soc
2025-09-14 feat: finish basic schematic, need to re-check
    Update README.md
2025-09-14 feat: basic board layout finished
2025-09-14 feat: routing part 1
2025-10-04 feat: routing part 2
2025-12-04 feat: attempt to finish routing
2025-12-04 feat: change to use esp32-s3 tempel
2026-01-09 feat: finish routing v3 prototype 1
2026-02-02 feat: update schematic svg
2026-02-02 feat: add led indicator
2026-03-12 feat: create esp32 tmd from slint embedded sample project
2026-03-14 feat: add draw buffer backend
2026-03-14 feat: slint with esp32s3 async poc is working
2026-03-14 feat: copying printer demo
2026-03-15 feat: add input and keypress event
2026-03-17 chore: remove gerber
